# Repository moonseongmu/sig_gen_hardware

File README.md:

# Software based function generator

PDF schematics are available [here](sig_gen_schematic.pdf). Design notes and component selection rationalisations are [here](design_notes.md).

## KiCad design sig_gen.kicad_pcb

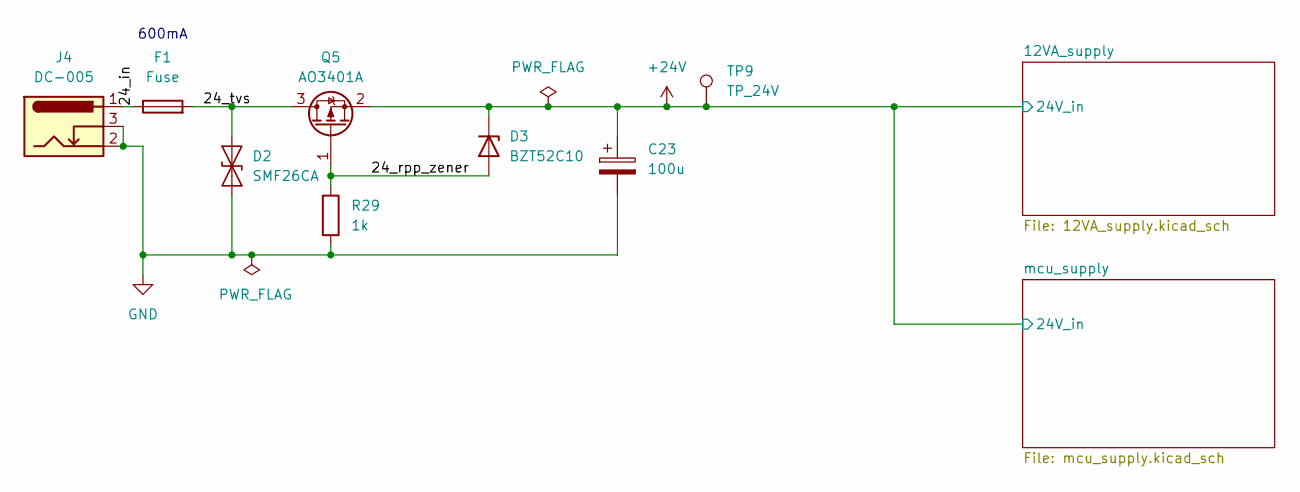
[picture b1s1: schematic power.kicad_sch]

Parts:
C23: 100u; CP_Elec_6.3x7.7; Manufacture Part Number UWT1V101MCL1GS; LCSC C125975
D2: SMF26CA; D_SOD-123F; Manufacture Part Number SMF26CA; LCSC C19077516
D3: BZT52C10; D_SOD-123F; Manufacture Part Number BZT52C10; LCSC C19077408
F1: Fuse; XFCN XF-155 SMD Fuseholder 2410; Manufacture Part Number XF-155; LCSC C41371860
J4: DC-005; Manufacture Part Number DC-005-A200; LCSC C720557
Q5: AO3401A; SOT-23; Manufacture Part Number AO3401A; LCSC C15127
R29: 1k; R_0805_2012Metric; Manufacture Part Number 0805W8F1001T5E; LCSC C17513
TP9: TP_24V; TestPoint_Pad_D1.0mm

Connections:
+24V: C23.1, D3.1 (K), Q5.2 (S), TP9.1 (1_1); also elsewhere on the board
/power/24_in: F1.1, J4.1
/power/24_rpp_zener: D3.2 (A), Q5.1 (G), R29.1
/power/24_tvs: D2.2 (A2), F1.2, Q5.3 (D)
GND: C23.2, D2.1 (A1), J4.2, J4.3, R29.2; also elsewhere on the board

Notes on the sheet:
600mA

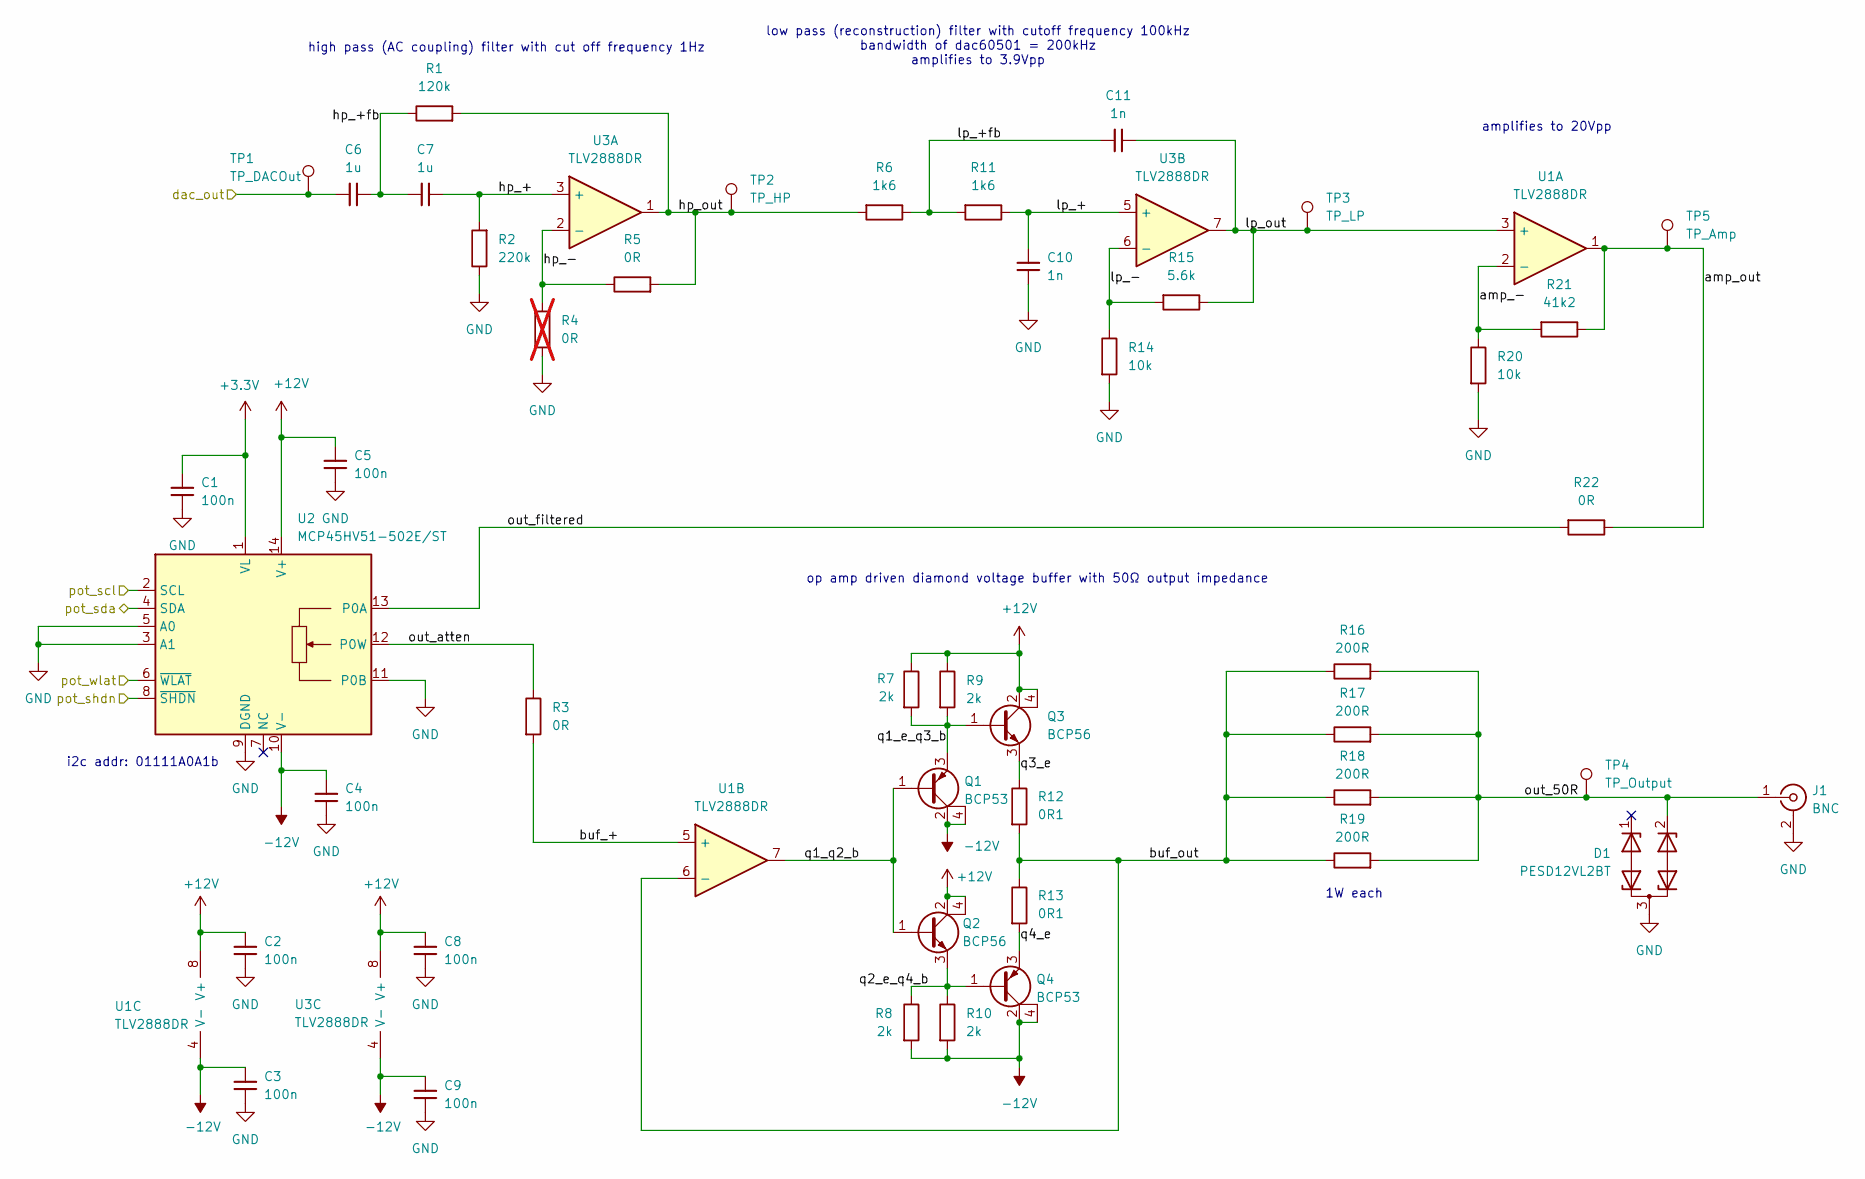
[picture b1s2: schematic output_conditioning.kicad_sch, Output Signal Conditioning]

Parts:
C1, C2, C3, C4, C5, C8, C9: 100n; C_0603_1608Metric; Manufacture Part Number CL10B104KB8NNNC; LCSC C1591
C6, C7: 1u; C_0805_2012Metric; Manufacture Part Number CC0805KKX7R9BB105; LCSC C91185
C10, C11: 1n; C_0805_2012Metric; Manufacture Part Number CL21B102KBCNNNC; LCSC C46653
D1: PESD12VL2BT; SOT-23; Manufacture Part Number PESD12VL2BT,215; LCSC C53428
J1: BNC; KH_BNC50-3511; Manufacture Part Number KH-BNC50-3511; LCSC C2837587
Q1, Q4: BCP53; SOT-223; Manufacture Part Number BCP53-16; LCSC C85085
Q2, Q3: BCP56; SOT-223; Manufacture Part Number BCP56-16; LCSC C92221
R1: 120k; R_0805_2012Metric; Manufacture Part Number 0805W8F1203T5E; LCSC C17436
R2: 220k; R_0805_2012Metric; Manufacture Part Number 0805W8F2203T5E; LCSC C17556
R3, R5, R22: 0R; R_0805_2012Metric; Manufacture Part Number 0805W8F0000T5E; LCSC C17477
R4: 0R; R_0805_2012Metric; Manufacture Part Number 0805W8F0000T5E; LCSC C17477; not fitted
R6, R11: 1k6; R_0805_2012Metric; Manufacture Part Number 0805W8F1601T5E; LCSC C17394
R7, R8, R9, R10: 2k; R_1206_3216Metric; Manufacture Part Number 1206W4F2001T5E; LCSC C17944
R12, R13: 0R1; R_1206_3216Metric; Manufacture Part Number 1206W4F100LT5E; LCSC C25334
R14, R20: 10k; R_0805_2012Metric; Manufacture Part Number 0805W8F1002T5E; LCSC C17414
R15: 5.6k; R_0805_2012Metric; Manufacture Part Number 0805W8F5601T5E; LCSC C4382
R16, R17, R18, R19: 200R; R_1210_3225Metric; Manufacture Part Number 1210W2F2000T5E; LCSC C55914
R21: 41k2; R_0805_2012Metric; Manufacture Part Number 0805W8F4122T5E; LCSC C17682
TP1: TP_DACOut; TestPoint_Pad_D1.0mm
TP2: TP_HP; TestPoint_Pad_D1.0mm
TP3: TP_LP; TestPoint_Pad_D1.0mm
TP4: TP_Output; TestPoint_Pad_D1.0mm
TP5: TP_Amp; TestPoint_Pad_D1.0mm
U1, U3: TLV2888DR; TI SOIC-8 (D); Manufacture Part Number TLV2888DR; LCSC C43687242
U2: MCP45HV51-502E/ST; TSSOP-14_4.4x5mm_P0.65mm; Manufacture Part Number MCP45HV51-502E/ST; LCSC C637119

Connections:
+3.3V: C1.1, U2.1 (VL); also elsewhere on the board
+12V: C2.1, C5.1, C8.1, Q2.2 (C), Q2.4 (C), Q3.2 (C), Q3.4 (C), R7.1, R9.1, U1.8 (V+), U2.14 (V+), U3.8 (V+); also elsewhere on the board
-12V: C3.1, C4.1, C9.1, Q1.2 (C), Q1.4 (C), Q4.2 (C), Q4.4 (C), R8.2, R10.2, U1.4 (V-), U2.10 (V-), U3.4 (V-); also elsewhere on the board
/microcontroller/dac_out: C6.2, TP1.1 (1_1); also elsewhere on the board
/microcontroller/pot_scl: U2.2 (SCL); also elsewhere on the board
/microcontroller/pot_sda: U2.4 (SDA); also elsewhere on the board
/microcontroller/pot_shdn: U2.8 (~SHDN); also elsewhere on the board
/microcontroller/pot_wlat: U2.6 (~WLAT); also elsewhere on the board
/output_conditioning/amp_-: R20.1, R21.2, U1.2 (-)
/output_conditioning/amp_out: R21.1, R22.1, TP5.1 (1_1), U1.1
/output_conditioning/buf_+: R3.2, U1.5 (+)
/output_conditioning/buf_out: R12.2, R13.1, R16.1, R17.1, R18.1, R19.1, U1.6 (-)
/output_conditioning/hp_+: C7.1, R2.2, U3.3 (+)
/output_conditioning/hp_+fb: C6.1, C7.2, R1.1
/output_conditioning/hp_-: R4.2, R5.1, U3.2 (-)
/output_conditioning/hp_out: R1.2, R5.2, R6.2, TP2.1 (1_1), U3.1
/output_conditioning/lp_+: C10.1, R11.1, U3.5 (+)
/output_conditioning/lp_+fb: C11.2, R6.1, R11.2
/output_conditioning/lp_-: R14.1, R15.2, U3.6 (-)
/output_conditioning/lp_out: C11.1, R15.1, TP3.1 (1_1), U1.3 (+), U3.7
/output_conditioning/out_50R: D1.2 (K), J1.1 (In), R16.2, R17.2, R18.2, R19.2, TP4.1 (1_1)
/output_conditioning/out_atten: R3.1, U2.12 (P0W)
/output_conditioning/out_filtered: R22.2, U2.13 (P0A)
/output_conditioning/q1_e_q3_b: Q1.3 (E), Q3.1 (B), R7.2, R9.2
/output_conditioning/q1_q2_b: Q1.1 (B), Q2.1 (B), U1.7
/output_conditioning/q2_e_q4_b: Q2.3 (E), Q4.1 (B), R8.1, R10.1
/output_conditioning/q3_e: Q3.3 (E), R12.1
/output_conditioning/q4_e: Q4.3 (E), R13.2
GND: C1.2, C2.2, C3.2, C4.2, C5.2, C8.2, C9.2, C10.2, D1.3 (A), J1.2 (Ext), R2.1, R4.1, R14.2, R20.2, U2.3 (A1), U2.5 (A0), U2.9 (DGND), U2.11 (P0B); also elsewhere on the board

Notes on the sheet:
high pass (AC coupling) filter with cut off frequency 1Hz
op amp driven diamond voltage buffer with 50Ω output impedance
amplifies to 20Vpp
low pass (reconstruction) filter with cutoff frequency 100kHz bandwidth of dac60501 = 200kHz amplifies to 3.9Vpp
i2c addr: 01111A0A1b
1W each

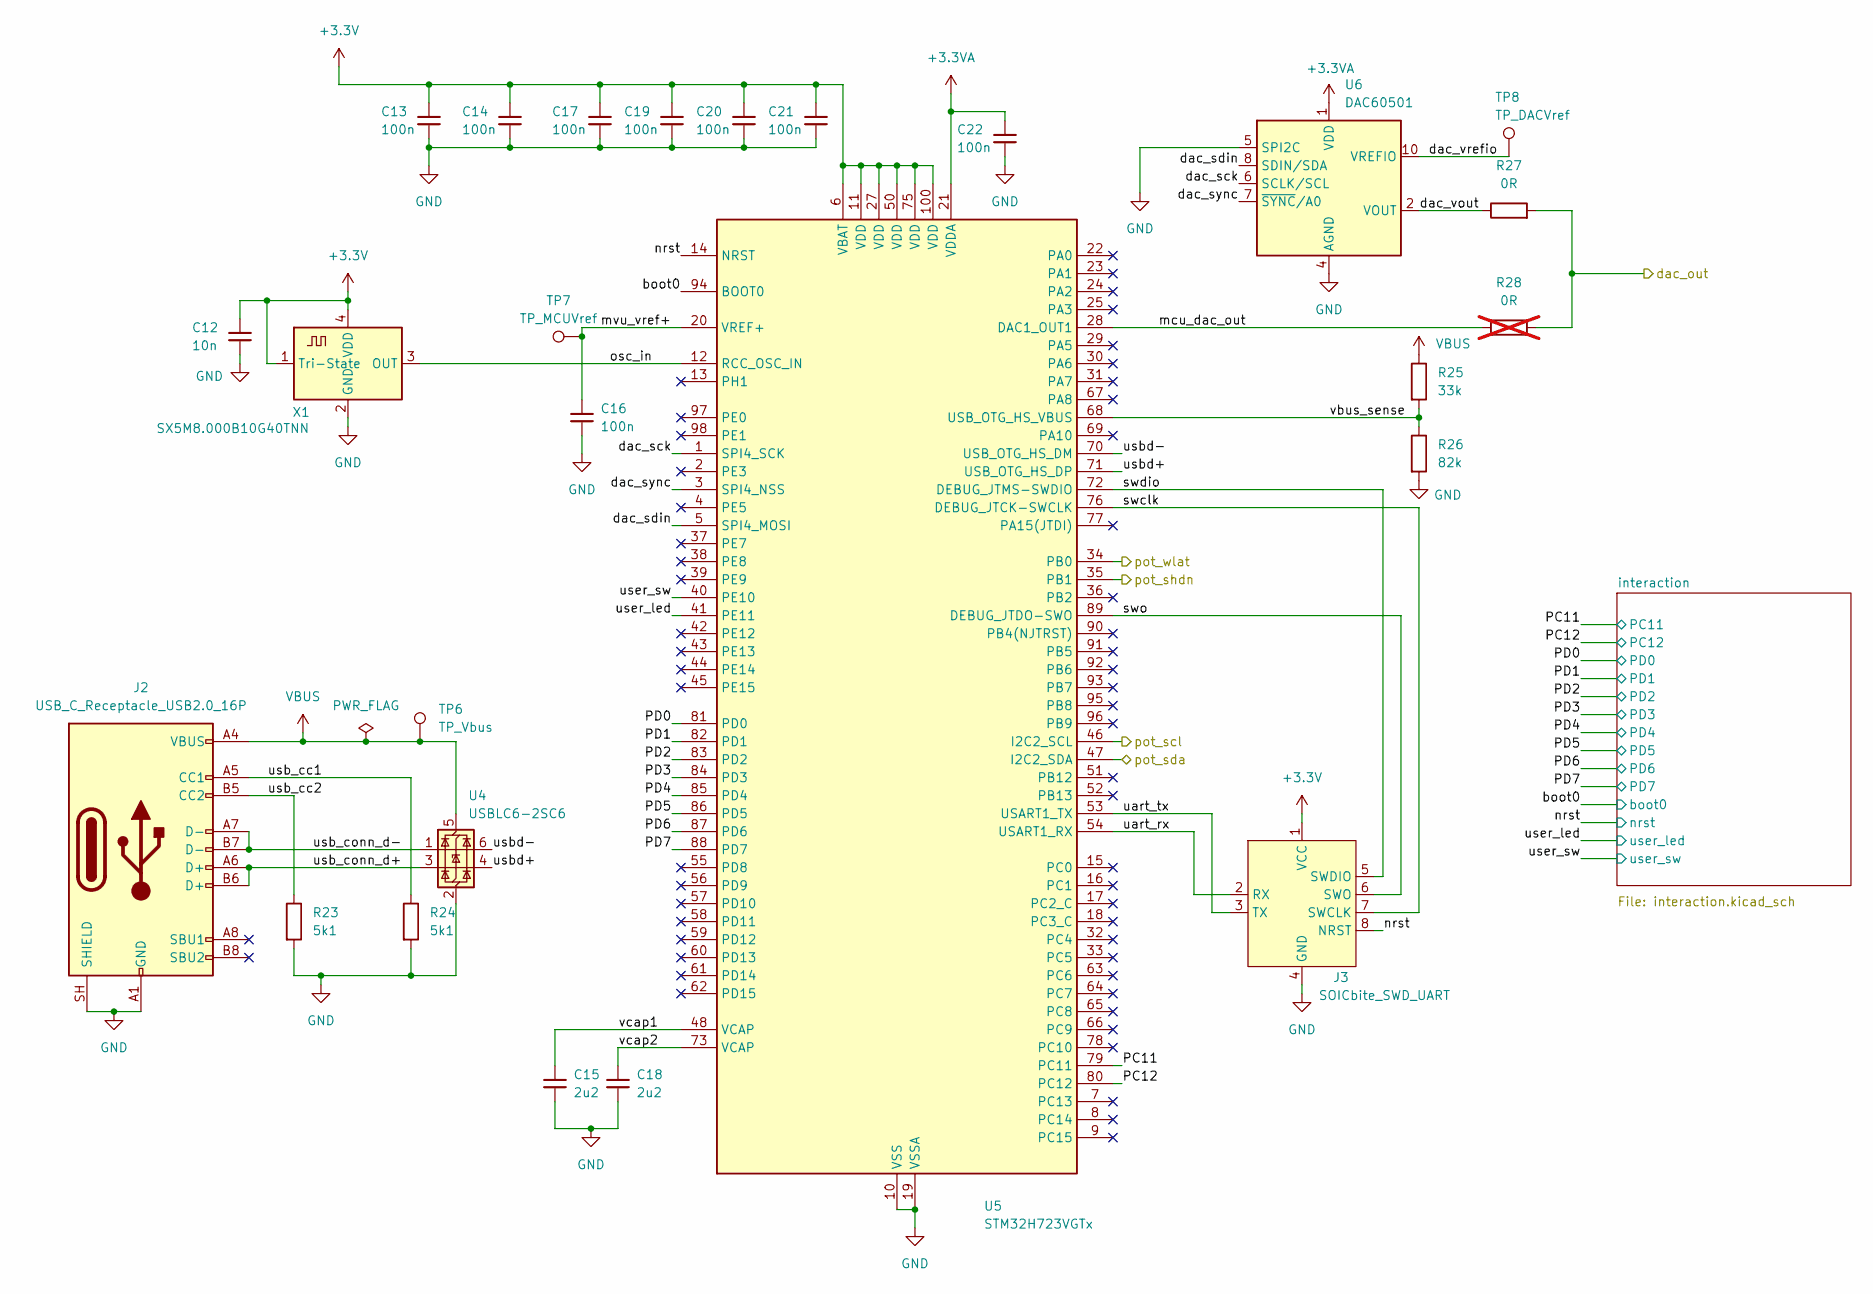
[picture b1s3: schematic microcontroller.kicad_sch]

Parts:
C12: 10n; C_0603_1608Metric
C13, C14, C16, C17, C19, C20, C21, C22: 100n; C_0603_1608Metric
C15, C18: 2u2; C_0805_2012Metric
J2: USB_C_Receptacle_USB2.0_16P; USB_C_Receptacle_G-Switch_GT-USB-7010ASV
J3: SOICbite_SWD_UART; SOIC_clipProgSmall
R23, R24: 5k1; R_0805_2012Metric
R25: 33k; R_0805_2012Metric
R26: 82k; R_0805_2012Metric
R27: 0R; R_0805_2012Metric
R28: 0R; R_0805_2012Metric; not fitted
TP6: TP_Vbus; TestPoint_Pad_D1.0mm
TP7: TP_MCUVref; TestPoint_Pad_D1.0mm
TP8: TP_DACVref; TestPoint_Pad_D1.0mm
U4: USBLC6-2SC6; SOT-23-6
U5: STM32H723VGTx; LQFP-100_14x14mm_P0.5mm
U6: DAC60501; TI VSSOP-10 (DGS)
X1: SX5M8.000B10G40TNN; SCTF 5C Hand_solder

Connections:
+3.3V: C12.2, C13.2, C14.2, C17.2, C19.2, C20.2, C21.2, J3.1 (VCC), U5.6 (VBAT), U5.11 (VDD), U5.27 (VDD), U5.50 (VDD), U5.75 (VDD), U5.100 (VDD), X1.1 (Tri-State), X1.4 (VDD); also elsewhere on the board
+3.3VA: C22.2, U5.21 (VDDA), U6.1 (VDD); also elsewhere on the board
/microcontroller/PC11: U5.79 (PC11); also elsewhere on the board
/microcontroller/PC12: U5.80 (PC12); also elsewhere on the board
/microcontroller/PD0: U5.81 (PD0); also elsewhere on the board
/microcontroller/PD1: U5.82 (PD1); also elsewhere on the board
/microcontroller/PD2: U5.83 (PD2); also elsewhere on the board
/microcontroller/PD3: U5.84 (PD3); also elsewhere on the board
/microcontroller/PD4: U5.85 (PD4); also elsewhere on the board
/microcontroller/PD5: U5.86 (PD5); also elsewhere on the board
/microcontroller/PD6: U5.87 (PD6); also elsewhere on the board
/microcontroller/PD7: U5.88 (PD7); also elsewhere on the board
/microcontroller/boot0: U5.94 (BOOT0); also elsewhere on the board
/microcontroller/dac_out: R27.2, R28.2; also elsewhere on the board
/microcontroller/dac_sck: U5.1 (SPI4_SCK), U6.6 (SCLK/SCL)
/microcontroller/dac_sdin: U5.5 (SPI4_MOSI), U6.8 (SDIN/SDA)
/microcontroller/dac_sync: U5.3 (SPI4_NSS), U6.7 (~SYNC/A0)
/microcontroller/dac_vout: R27.1, U6.2 (VOUT)
/microcontroller/dac_vrefio: TP8.1 (1_1), U6.10 (VREFIO)
/microcontroller/mcu_dac_out: R28.1, U5.28 (DAC1_OUT1)
/microcontroller/mvu_vref+: C16.2, TP7.1 (1_1), U5.20 (VREF+)
/microcontroller/nrst: J3.8 (NRST), U5.14 (NRST); also elsewhere on the board
/microcontroller/osc_in: U5.12 (RCC_OSC_IN), X1.3 (OUT)
/microcontroller/pot_scl: U5.46 (I2C2_SCL); also elsewhere on the board
/microcontroller/pot_sda: U5.47 (I2C2_SDA); also elsewhere on the board
/microcontroller/pot_shdn: U5.35 (PB1); also elsewhere on the board
/microcontroller/pot_wlat: U5.34 (PB0); also elsewhere on the board
/microcontroller/swclk: J3.7 (SWCLK), U5.76 (DEBUG_JTCK-SWCLK)
/microcontroller/swdio: J3.5 (SWDIO), U5.72 (DEBUG_JTMS-SWDIO)
/microcontroller/swo: J3.6 (SWO), U5.89 (DEBUG_JTDO-SWO)
/microcontroller/uart_rx: J3.2 (RX), U5.54 (USART1_RX)
/microcontroller/uart_tx: J3.3 (TX), U5.53 (USART1_TX)
/microcontroller/usb_cc1: J2.A5 (CC1), R24.1
/microcontroller/usb_cc2: J2.B5 (CC2), R23.1
/microcontroller/usb_conn_d+: J2.A6 (D+), J2.B6 (D+), U4.3 (I/O2)
/microcontroller/usb_conn_d-: J2.A7 (D-), J2.B7 (D-), U4.1 (I/O1)
/microcontroller/usbd+: U4.4 (I/O2), U5.71 (USB_OTG_HS_DP)
/microcontroller/usbd-: U4.6 (I/O1), U5.70 (USB_OTG_HS_DM)
/microcontroller/user_led: U5.41 (PE11); also elsewhere on the board
/microcontroller/user_sw: U5.40 (PE10); also elsewhere on the board
/microcontroller/vbus_sense: R25.2, R26.1, U5.68 (USB_OTG_HS_VBUS)
/microcontroller/vcap1: C15.1, U5.48 (VCAP)
/microcontroller/vcap2: C18.1, U5.73 (VCAP)
GND: C12.1, C13.1, C14.1, C15.2, C16.1, C17.1, C18.2, C19.1, C20.1, C21.1, C22.1, J2.A1 (GND), J2.A12 (GND), J2.B1 (GND), J2.B12 (GND), J2.SH (SHIELD), J3.4 (GND), R23.2, R24.2, R26.2, U4.2 (GND), U5.10 (VSS), U5.19 (VSSA), U5.26 (VSS), U5.49 (VSS), U5.74 (VSS), U5.99 (VSS), U6.4 (AGND), U6.5 (SPI2C), X1.2 (GND); also elsewhere on the board
VBUS: J2.A4 (VBUS), J2.A9 (VBUS), J2.B4 (VBUS), J2.B9 (VBUS), R25.1, TP6.1 (1_1), U4.5 (VBUS)

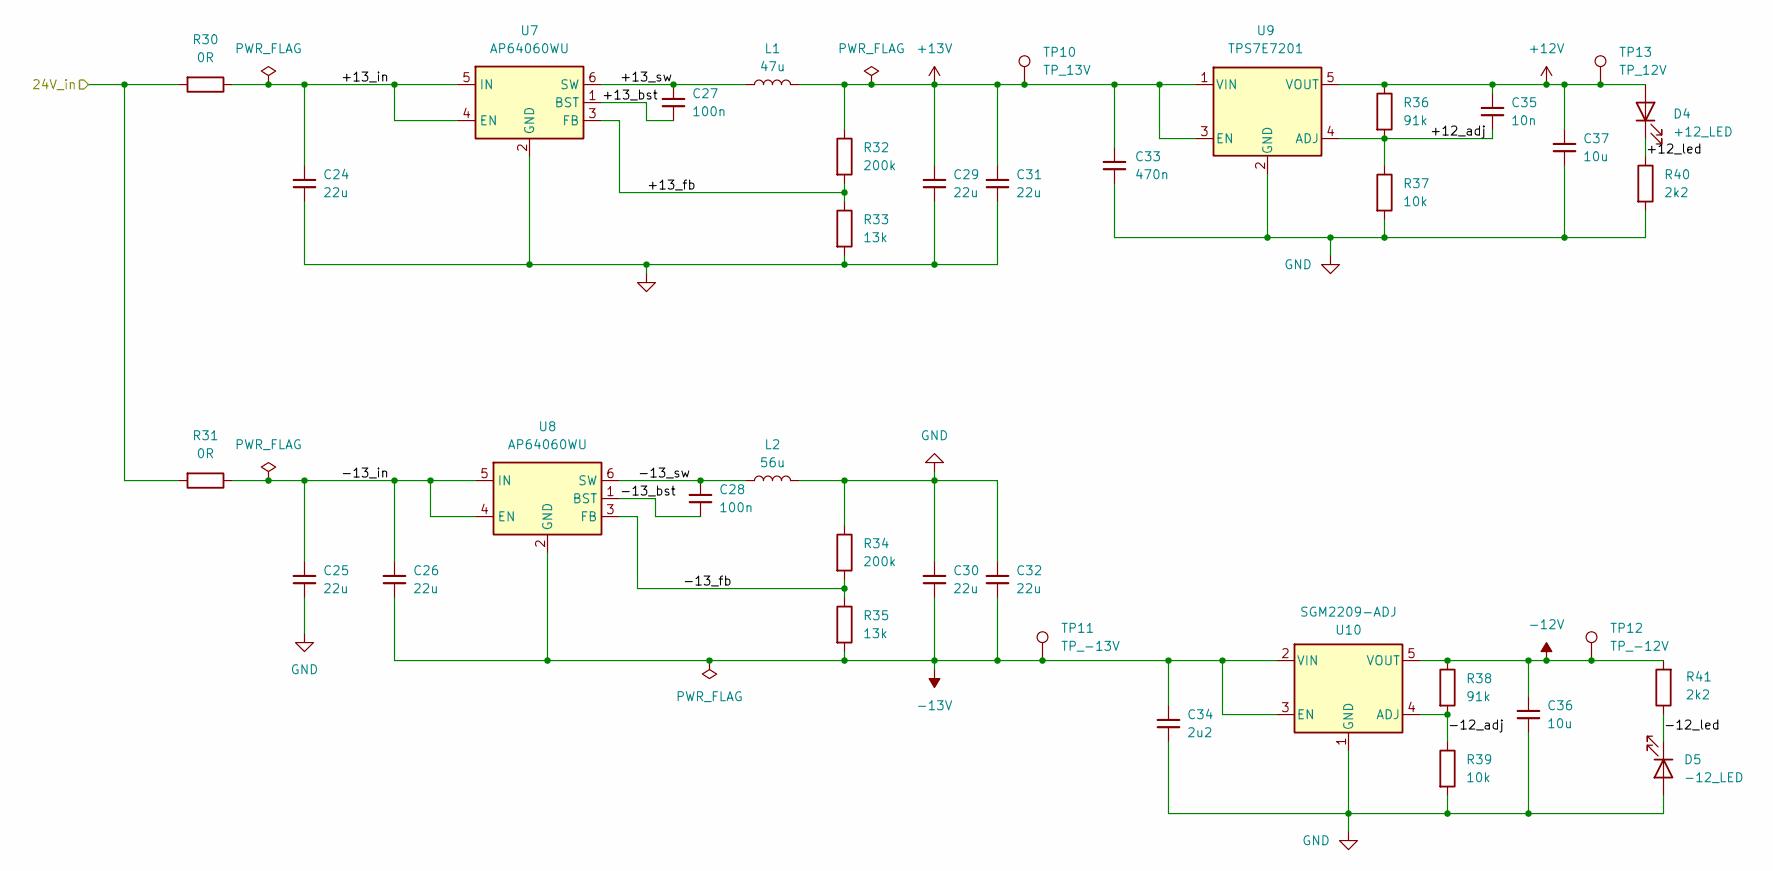
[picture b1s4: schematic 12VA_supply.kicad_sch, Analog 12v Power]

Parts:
C24, C25, C26, C29, C30, C31, C32: 22u; C_1206_3216Metric; Manufacture Part Number CL31A226KAHNNNE; LCSC C12891
C27, C28: 100n; C_0603_1608Metric; Manufacture Part Number CL10B104KB8NNNC; LCSC C1591
C33: 470n; C_0805_2012Metric; Manufacture Part Number CL21B474KBFNNNE; LCSC C13967
C34: 2u2; C_0805_2012Metric; Manufacture Part Number CC0805KKX7R9BB225; LCSC C125847
C35: 10n; C_0805_2012Metric; Manufacture Part Number CC0805KRX7R9BB103; LCSC C83170
C36, C37: 10u; C_0805_2012Metric; Manufacture Part Number GRM21BR61H106KE43L; LCSC C440198
D4: +12_LED; LED_0805_2012Metric; Manufacture Part Number NCD0805R1; LCSC C84256
D5: -12_LED; LED_0805_2012Metric; Manufacture Part Number NCD0805R1; LCSC C84256
L1: 47u; L_Taiyo-Yuden_NR-60xx_HandSoldering; Manufacture Part Number LCXND6060WHL470MMG; LCSC C7295510
L2: 56u; L_APV_ANR4030_Hand_Solder; Manufacture Part Number ANR4030T560M; LCSC C55562543
R30, R31: 0R; R_0805_2012Metric; Manufacture Part Number 0805W8F0000T5E; LCSC C17477
R32, R34: 200k; R_0805_2012Metric; Manufacture Part Number 0805W8F2003T5E; LCSC C17539
R33, R35: 13k; R_0805_2012Metric; Manufacture Part Number 0805W8F1302T5E; LCSC C17455
R36, R38: 91k; R_0805_2012Metric; Manufacture Part Number 0805W8F9102T5E; LCSC C17866
R37, R39: 10k; R_0805_2012Metric; Manufacture Part Number 0805W8F1002T5E; LCSC C17414
R40, R41: 2k2; R_0805_2012Metric; Manufacture Part Number 0805W8F2201T5E; LCSC C17520
TP10: TP_13V; TestPoint_Pad_D1.0mm
TP11: TP_-13V; TestPoint_Pad_D1.0mm
TP12: TP_-12V; TestPoint_Pad_D1.0mm
TP13: TP_12V; TestPoint_Pad_D1.0mm
U7, U8: AP64060WU; TSOT-23-6; Manufacture Part Number AP64060WU-7; LCSC C6500862
U9: TPS7E7201; SOT-23-5; Manufacture Part Number TPS7E7201DBVR; LCSC C54887073
U10: SGM2209-ADJ; SOT-23-5; Manufacture Part Number SGM2209-ADJXN5G/TR; LCSC C5152788

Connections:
+12V: C35.1, C37.1, D4.2 (A), R36.1, TP13.1 (1_1), U9.5 (VOUT); also elsewhere on the board
+13V: C29.1, C31.1, C33.1, L1.2, R32.1, TP10.1 (1_1), U9.1 (VIN), U9.3 (EN)
+24V: R30.2, R31.2; also elsewhere on the board
-12V: C36.1, R38.1, R41.2, TP12.1 (1_1), U10.5 (VOUT); also elsewhere on the board
-13V: C26.2, C30.2, C32.2, C34.1, R35.2, TP11.1 (1_1), U8.2 (GND), U10.2 (VIN), U10.3 (EN)
/power/12VA_supply/+12_adj: C35.2, R36.2, R37.1, U9.4 (ADJ)
/power/12VA_supply/+12_led: D4.1 (K), R40.1
/power/12VA_supply/+13_bst: C27.2, U7.1 (BST)
/power/12VA_supply/+13_fb: R32.2, R33.1, U7.3 (FB)
/power/12VA_supply/+13_in: C24.1, R30.1, U7.4 (EN), U7.5 (IN)
/power/12VA_supply/+13_sw: C27.1, L1.1, U7.6 (SW)
/power/12VA_supply/-12_adj: R38.2, R39.1, U10.4 (ADJ)
/power/12VA_supply/-12_led: D5.1 (K), R41.1
/power/12VA_supply/-13_bst: C28.2, U8.1 (BST)
/power/12VA_supply/-13_fb: R34.2, R35.1, U8.3 (FB)
/power/12VA_supply/-13_in: C25.1, C26.1, R31.1, U8.4 (EN), U8.5 (IN)
/power/12VA_supply/-13_sw: C28.1, L2.1, U8.6 (SW)
GND: C24.2, C25.2, C29.2, C30.1, C31.2, C32.1, C33.2, C34.2, C36.2, C37.2, D5.2 (A), L2.2, R33.2, R34.1, R37.2, R39.2, R40.2, U7.2 (GND), U9.2 (GND), U10.1 (GND); also elsewhere on the board

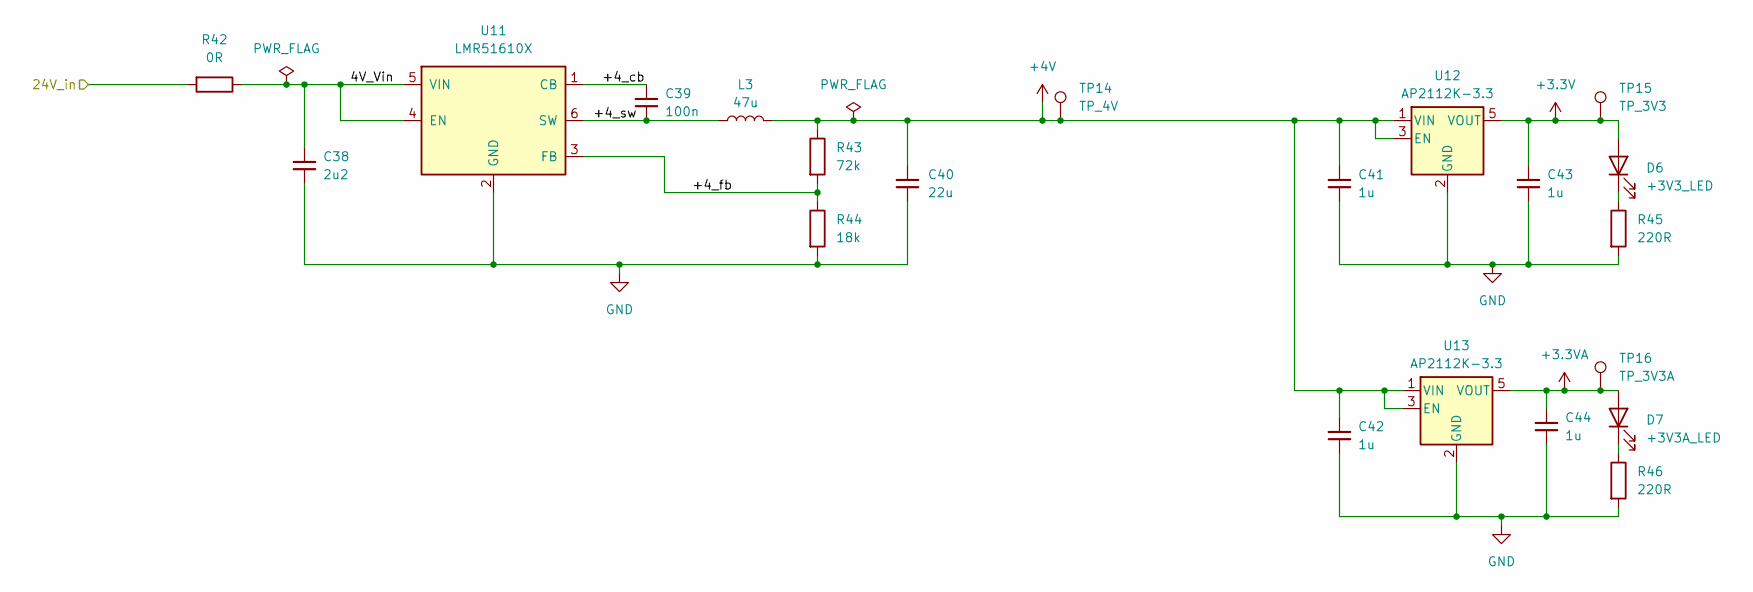
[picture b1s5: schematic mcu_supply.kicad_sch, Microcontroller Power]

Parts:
C38: 2u2; C_0805_2012Metric
C39: 100n; C_0603_1608Metric
C40: 22u; C_1210_3225Metric
C41, C42, C43, C44: 1u; C_0805_2012Metric
D6: +3V3_LED; LED_0805_2012Metric
D7: +3V3A_LED; LED_0805_2012Metric
L3: 47u; L_Taiyo-Yuden_NR-60xx_HandSoldering
R42: 0R; R_0805_2012Metric
R43: 72k; R_0805_2012Metric
R44: 18k; R_0805_2012Metric
R45, R46: 220R; R_0805_2012Metric
TP14: TP_4V; TestPoint_Pad_D1.0mm
TP15: TP_3V3; TestPoint_Pad_D1.0mm
TP16: TP_3V3A; TestPoint_Pad_D1.0mm
U11: LMR51610X; SOT-23-6
U12, U13: AP2112K-3.3; SOT-23-5

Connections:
+3.3V: C43.1, D6.2 (A), TP15.1 (1_1), U12.5 (VOUT); also elsewhere on the board
+3.3VA: C44.1, D7.2 (A), TP16.1 (1_1), U13.5 (VOUT); also elsewhere on the board
+4V: C40.1, C41.1, C42.1, L3.2, R43.1, TP14.1 (1_1), U12.1 (VIN), U12.3 (EN), U13.1 (VIN), U13.3 (EN)
+24V: R42.2; also elsewhere on the board
/power/mcu_supply/4V_Vin: C38.1, R42.1, U11.4 (EN), U11.5 (VIN)
/power/mcu_supply/+4_cb: C39.1, U11.1 (CB)
/power/mcu_supply/+4_fb: R43.2, R44.1, U11.3 (FB)
/power/mcu_supply/+4_sw: C39.2, L3.1, U11.6 (SW)
GND: C38.2, C40.2, C41.2, C42.2, C43.2, C44.2, R44.2, R45.2, R46.2, U11.2 (GND), U12.2 (GND), U13.2 (GND); also elsewhere on the board
unnamed: D6.1 (K), R45.1
unnamed: D7.1 (K), R46.1

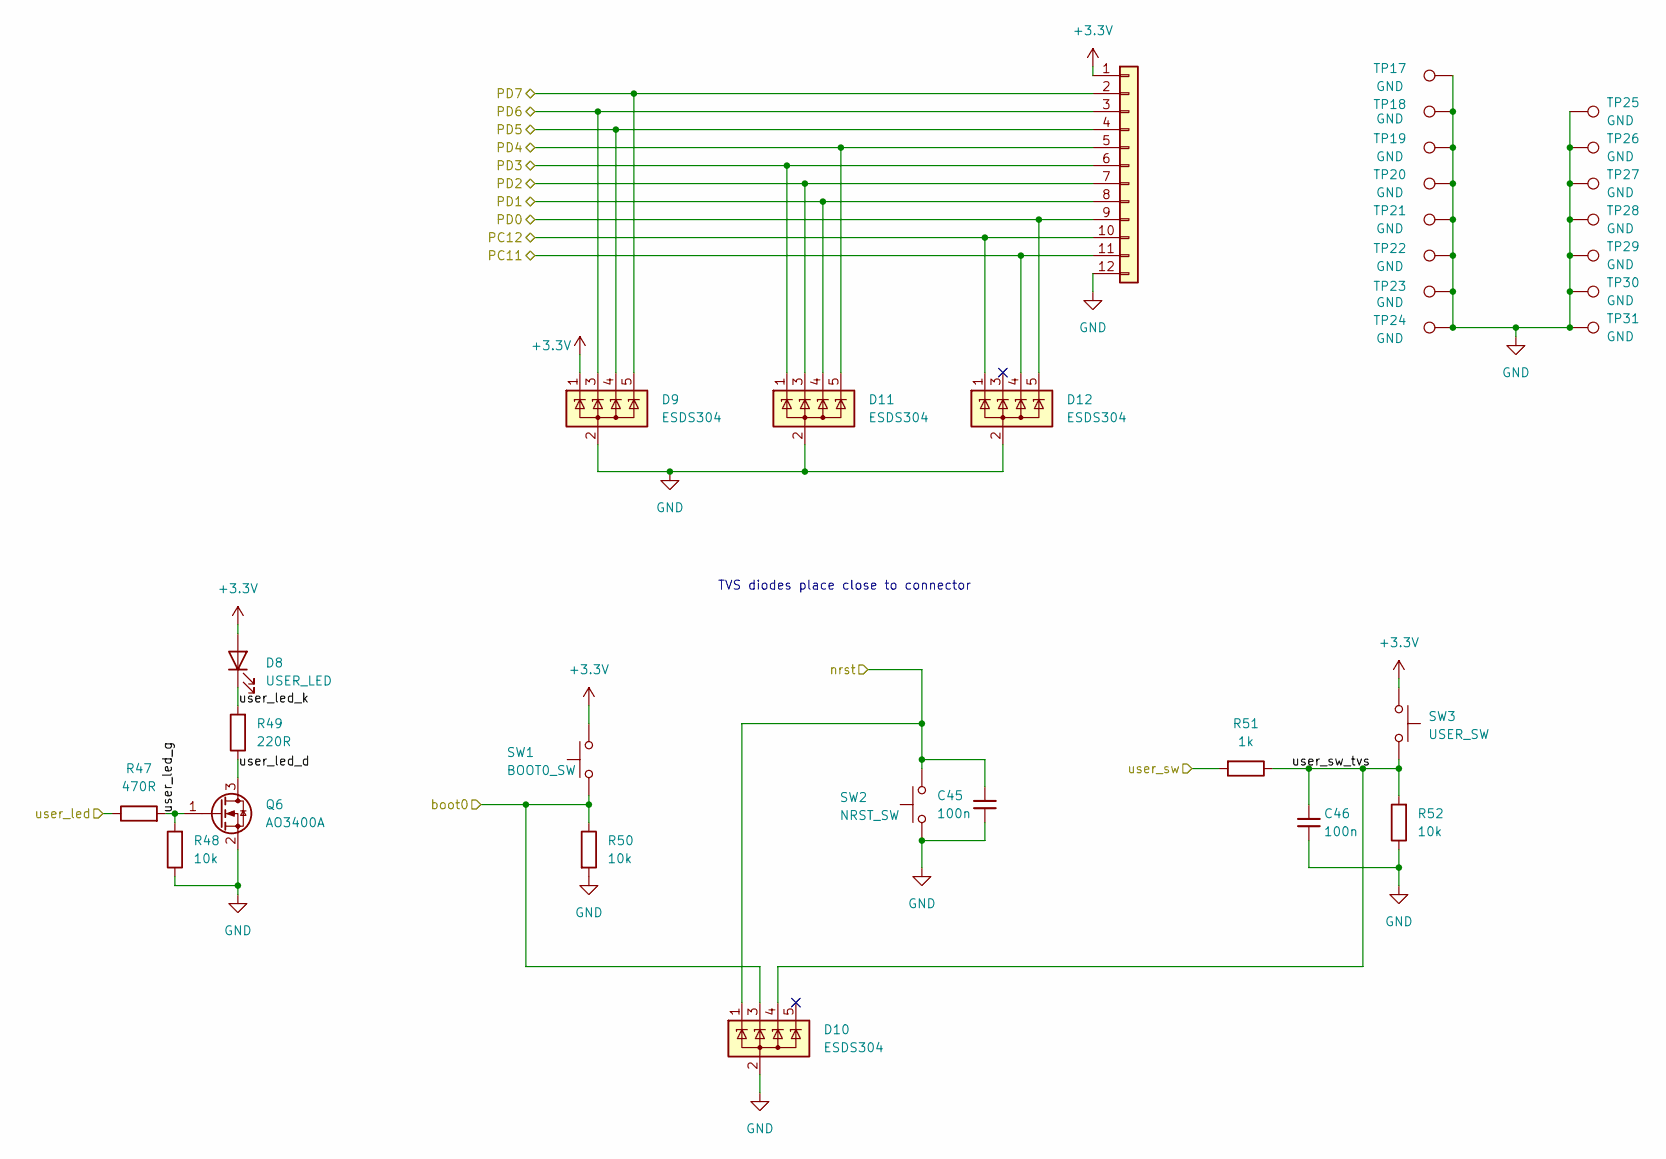
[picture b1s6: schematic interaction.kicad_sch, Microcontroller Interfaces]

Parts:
C45, C46: 100n; C_0603_1608Metric; Manufacture Part Number CL10B104KB8NNNC; LCSC C1591
D8: USER_LED; LED_0805_2012Metric; Manufacture Part Number NCD0805R1; LCSC C84256
D9, D10, D11, D12: ESDS304; SOT-23-5; Manufacture Part Number ESDS304DBVR; LCSC C1847869
J5: Conn_01x12; PinHeader_1x12_P2.54mm_Horizontal; Manufacture Part Number PZ254R-11-12P; LCSC C41413622
Q6: AO3400A; SOT-23; Manufacture Part Number AO3400A; LCSC C20917
R47: 470R; R_0805_2012Metric; Manufacture Part Number 0805W8F4700T5E; LCSC C17710
R48, R50, R52: 10k; R_0805_2012Metric; Manufacture Part Number 0805W8F1002T5E; LCSC C17414
R49: 220R; R_0805_2012Metric; Manufacture Part Number 0805W8F2200T5E; LCSC C17557
R51: 1k; R_0805_2012Metric; Manufacture Part Number 0805W8F1001T5E; LCSC C17513
SW1: BOOT0_SW; SW_SPST_TS-1088-xR020; Manufacture Part Number TS-1088-AR02016; LCSC C720477
SW2: NRST_SW; SW_SPST_TS-1088-xR020; Manufacture Part Number TS-1088-AR02016; LCSC C720477
SW3: USER_SW; SW_SPST_TS-1088-xR020; Manufacture Part Number TS-1088-AR02016; LCSC C720477
TP17, TP18, TP19, TP20, TP21, TP22, TP23, TP24, TP25, TP26, TP27, TP28, TP29, TP30, TP31: GND; TestPoint_THTPad_1.0x1.0mm_Drill0.5mm

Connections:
+3.3V: D8.2 (A), D9.1 (K), J5.1, SW1.2, SW3.1; also elsewhere on the board
/microcontroller/PC11: D12.4 (K), J5.11; also elsewhere on the board
/microcontroller/PC12: D12.1 (K), J5.10; also elsewhere on the board
/microcontroller/PD0: D12.5 (K), J5.9; also elsewhere on the board
/microcontroller/PD1: D11.4 (K), J5.8; also elsewhere on the board
/microcontroller/PD2: D11.3 (K), J5.7; also elsewhere on the board
/microcontroller/PD3: D11.1 (K), J5.6; also elsewhere on the board
/microcontroller/PD4: D11.5 (K), J5.5; also elsewhere on the board
/microcontroller/PD5: D9.4 (K), J5.4; also elsewhere on the board
/microcontroller/PD6: D9.3 (K), J5.3; also elsewhere on the board
/microcontroller/PD7: D9.5 (K), J5.2; also elsewhere on the board
/microcontroller/boot0: D10.3 (K), R50.1, SW1.1; also elsewhere on the board
/microcontroller/interaction/user_led_d: Q6.3 (D), R49.1
/microcontroller/interaction/user_led_g: Q6.1 (G), R47.2, R48.2
/microcontroller/interaction/user_led_k: D8.1 (K), R49.2
/microcontroller/interaction/user_sw_tvs: C46.2, D10.4 (K), R51.1, R52.2, SW3.2
/microcontroller/nrst: C45.2, D10.1 (K), SW2.2; also elsewhere on the board
/microcontroller/user_led: R47.1; also elsewhere on the board
/microcontroller/user_sw: R51.2; also elsewhere on the board
GND: C45.1, C46.1, D9.2 (A), D10.2 (A), D11.2 (A), D12.2 (A), J5.12, Q6.2 (S), R48.1, R50.2, R52.1, SW2.1, TP17.1 (1_1), TP18.1 (1_1), TP19.1 (1_1), TP20.1 (1_1), TP21.1 (1_1), TP22.1 (1_1), TP23.1 (1_1), TP24.1 (1_1), TP25.1 (1_1), TP26.1 (1_1), TP27.1 (1_1), TP28.1 (1_1), TP29.1 (1_1), TP30.1 (1_1), TP31.1 (1_1); also elsewhere on the board

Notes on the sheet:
TVS diodes place close to connector

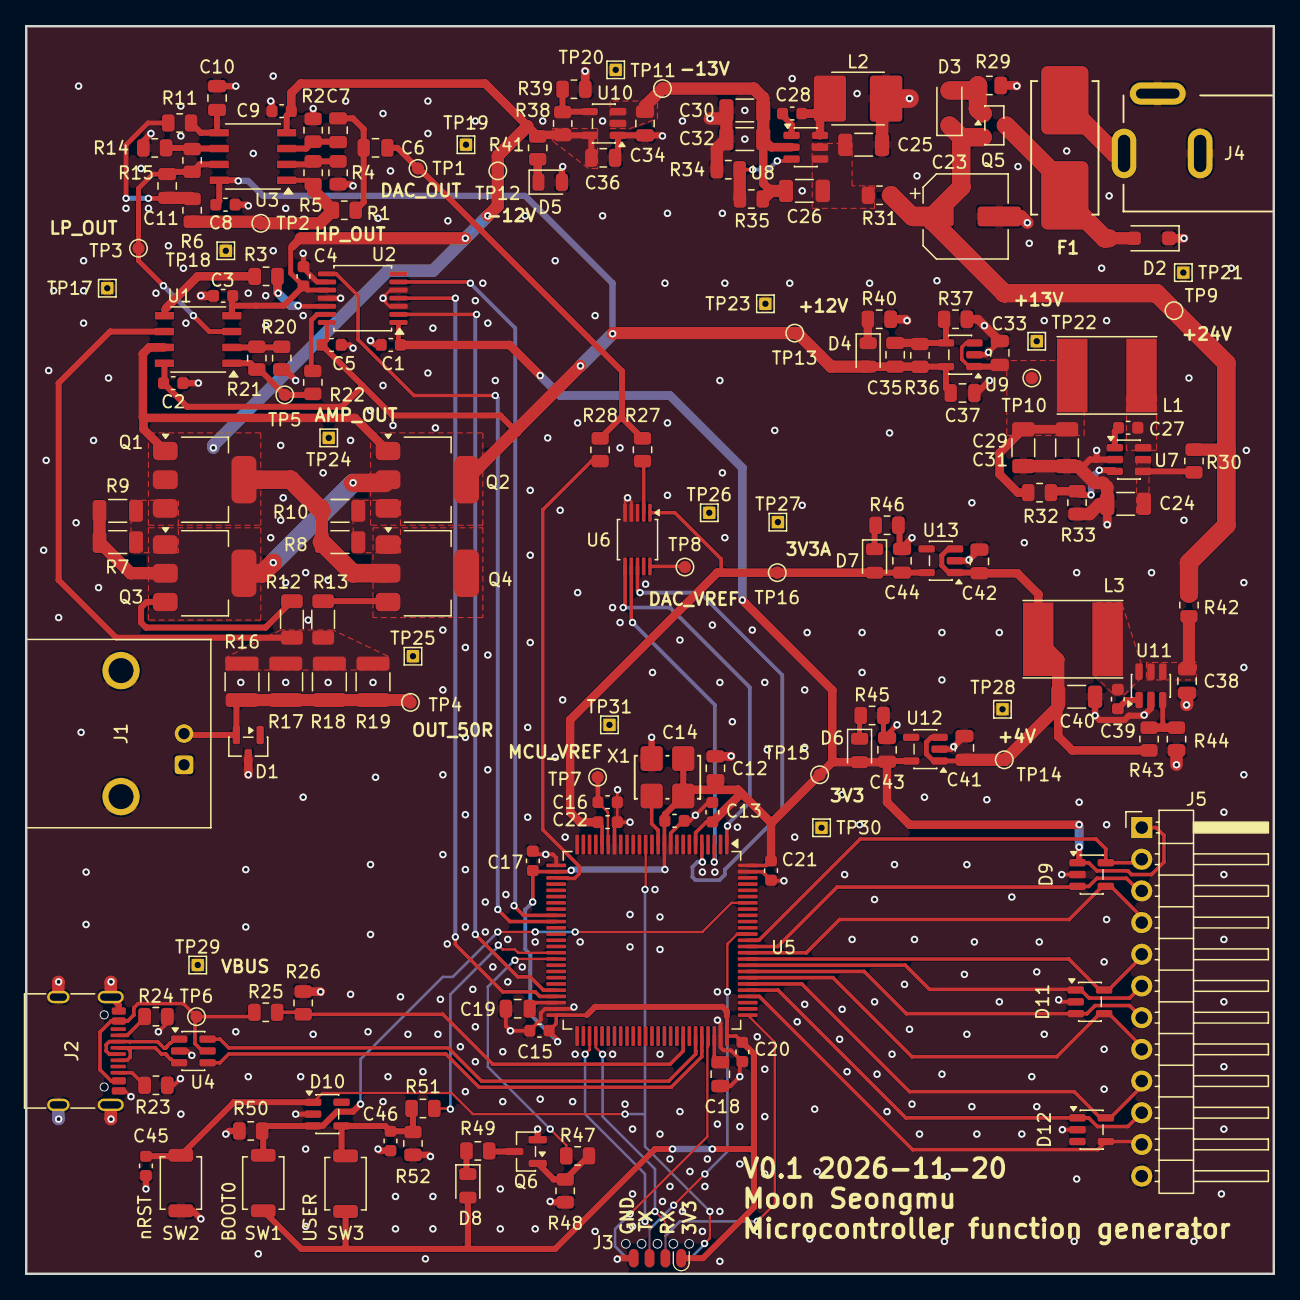
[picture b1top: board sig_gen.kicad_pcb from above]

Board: 4 copper layers, 100.0 x 100.0 mm, 173 parts (0 on the bottom side), 96 nets.

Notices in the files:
12VA_supply.kicad_sch:
Licensed under CERN-OHL-S V2
sig_gen.kicad_pcb:
CERN-OHL-S
